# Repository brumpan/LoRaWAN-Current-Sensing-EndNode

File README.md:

# LoRaWAN-Current-Sensing-EndNode

Traditionally, remote monitoring has been done using wired communications technologies such as ethernet and fiberoptics. In the last decade, low power narrow band radio communications technologies, such as LoRaWAN, have enabled wireless remote monitoring in microgrids.  Installing remote monitoring systems can be very costly using both wired or wireless communication schemes. Wired connections are expensive during installation and wireless connections are expensive during operation due to service subscriptions and may also require pre-existing infrastructure to operate. This project provides a modular solution for monitoring power output from photovoltaic panels remotely.

This page contains the design files and software for a current-sensing end node for photovoltaic panels in microgrids using the LoRaWAN network.

# Dependencies

https://github.com/ElectronicCats/Beelan-LoRaWAN.git

https://github.com/earlephilhower/arduino-pico.git

# Credits

This project constitutes partial fulfillment of the Senior Project Capstone, a prerequisite for obtaining a Bachelor's degree in Electrical Engineering from The Oregon Institute of Technology.

Project Members: Brendan Dickerson & Leo Zenuhin

Spring 2023

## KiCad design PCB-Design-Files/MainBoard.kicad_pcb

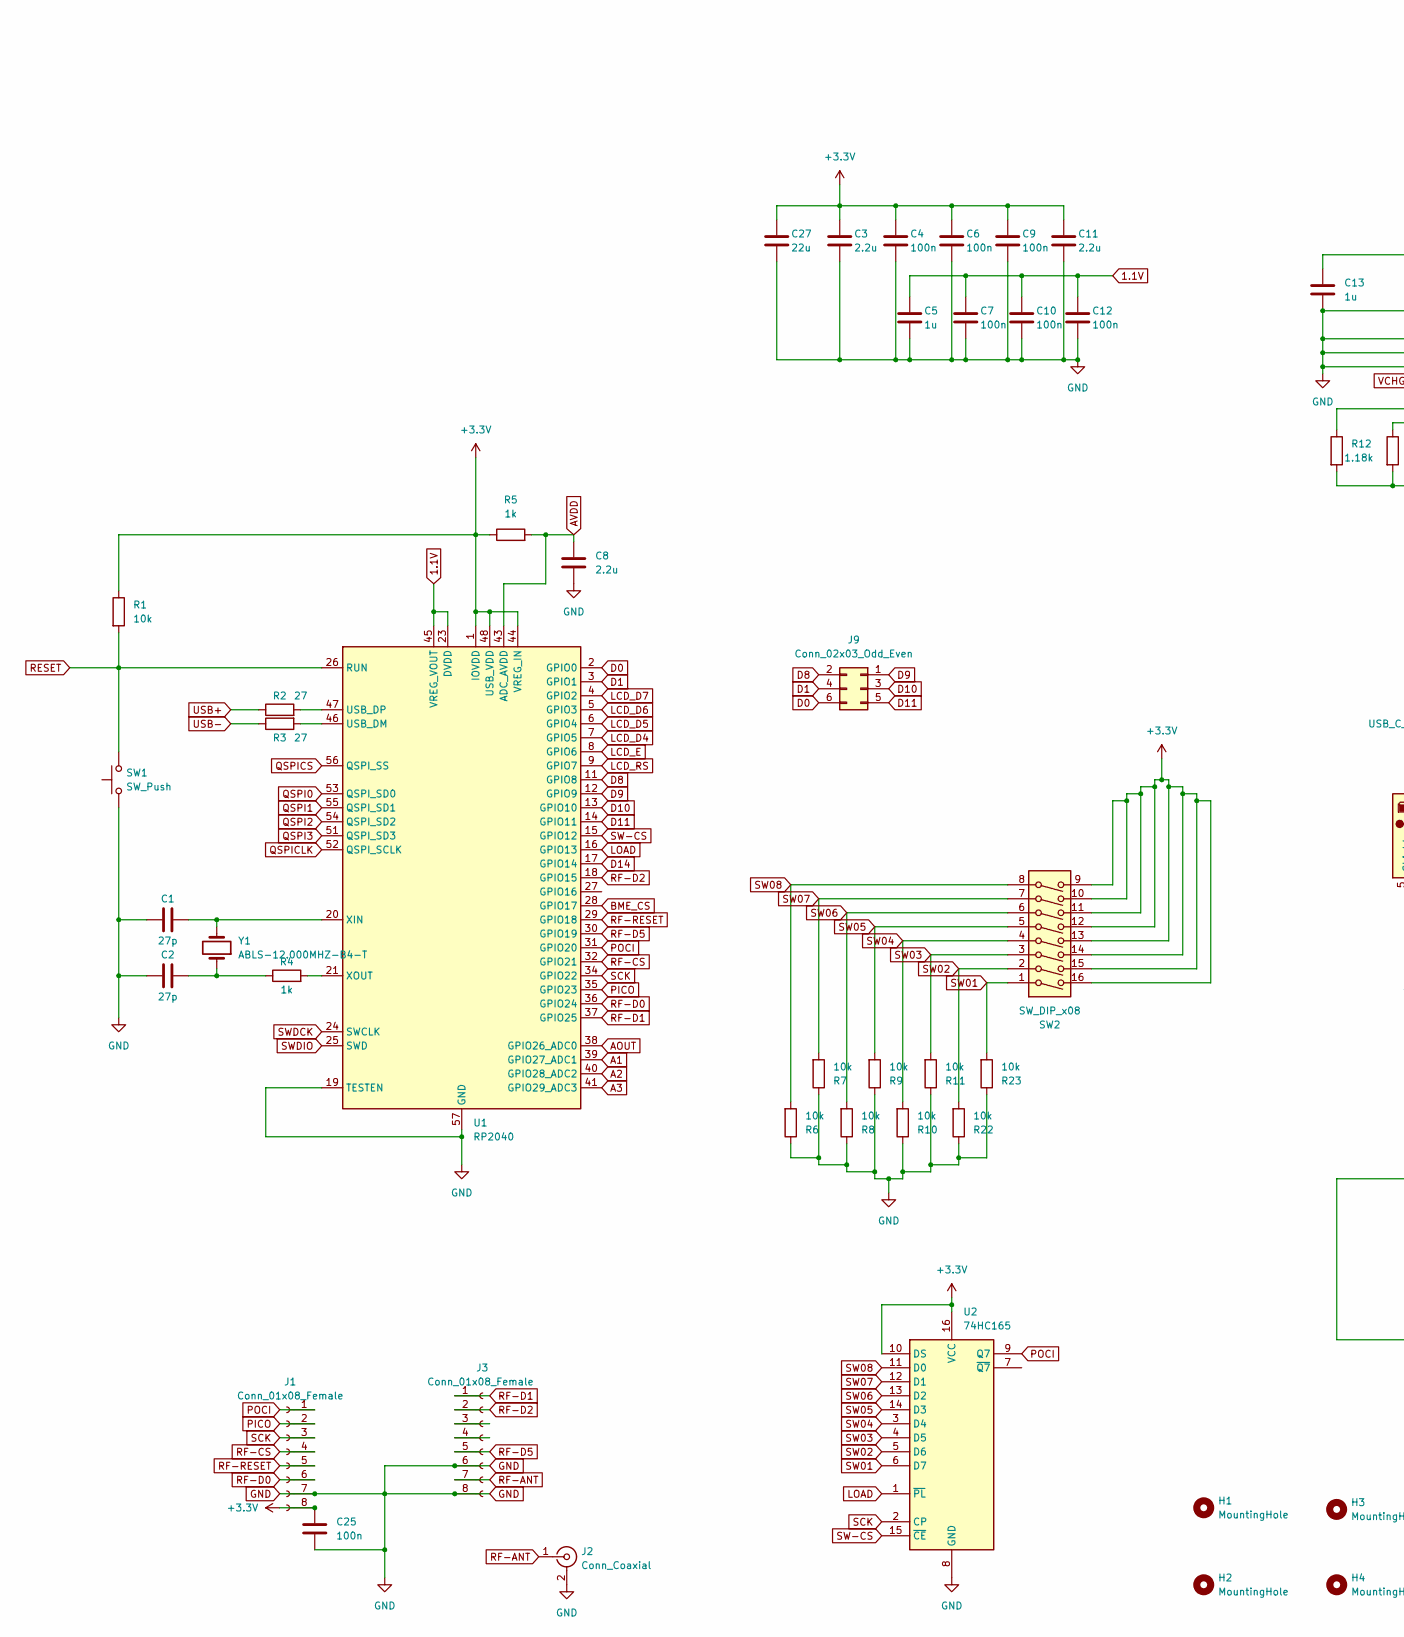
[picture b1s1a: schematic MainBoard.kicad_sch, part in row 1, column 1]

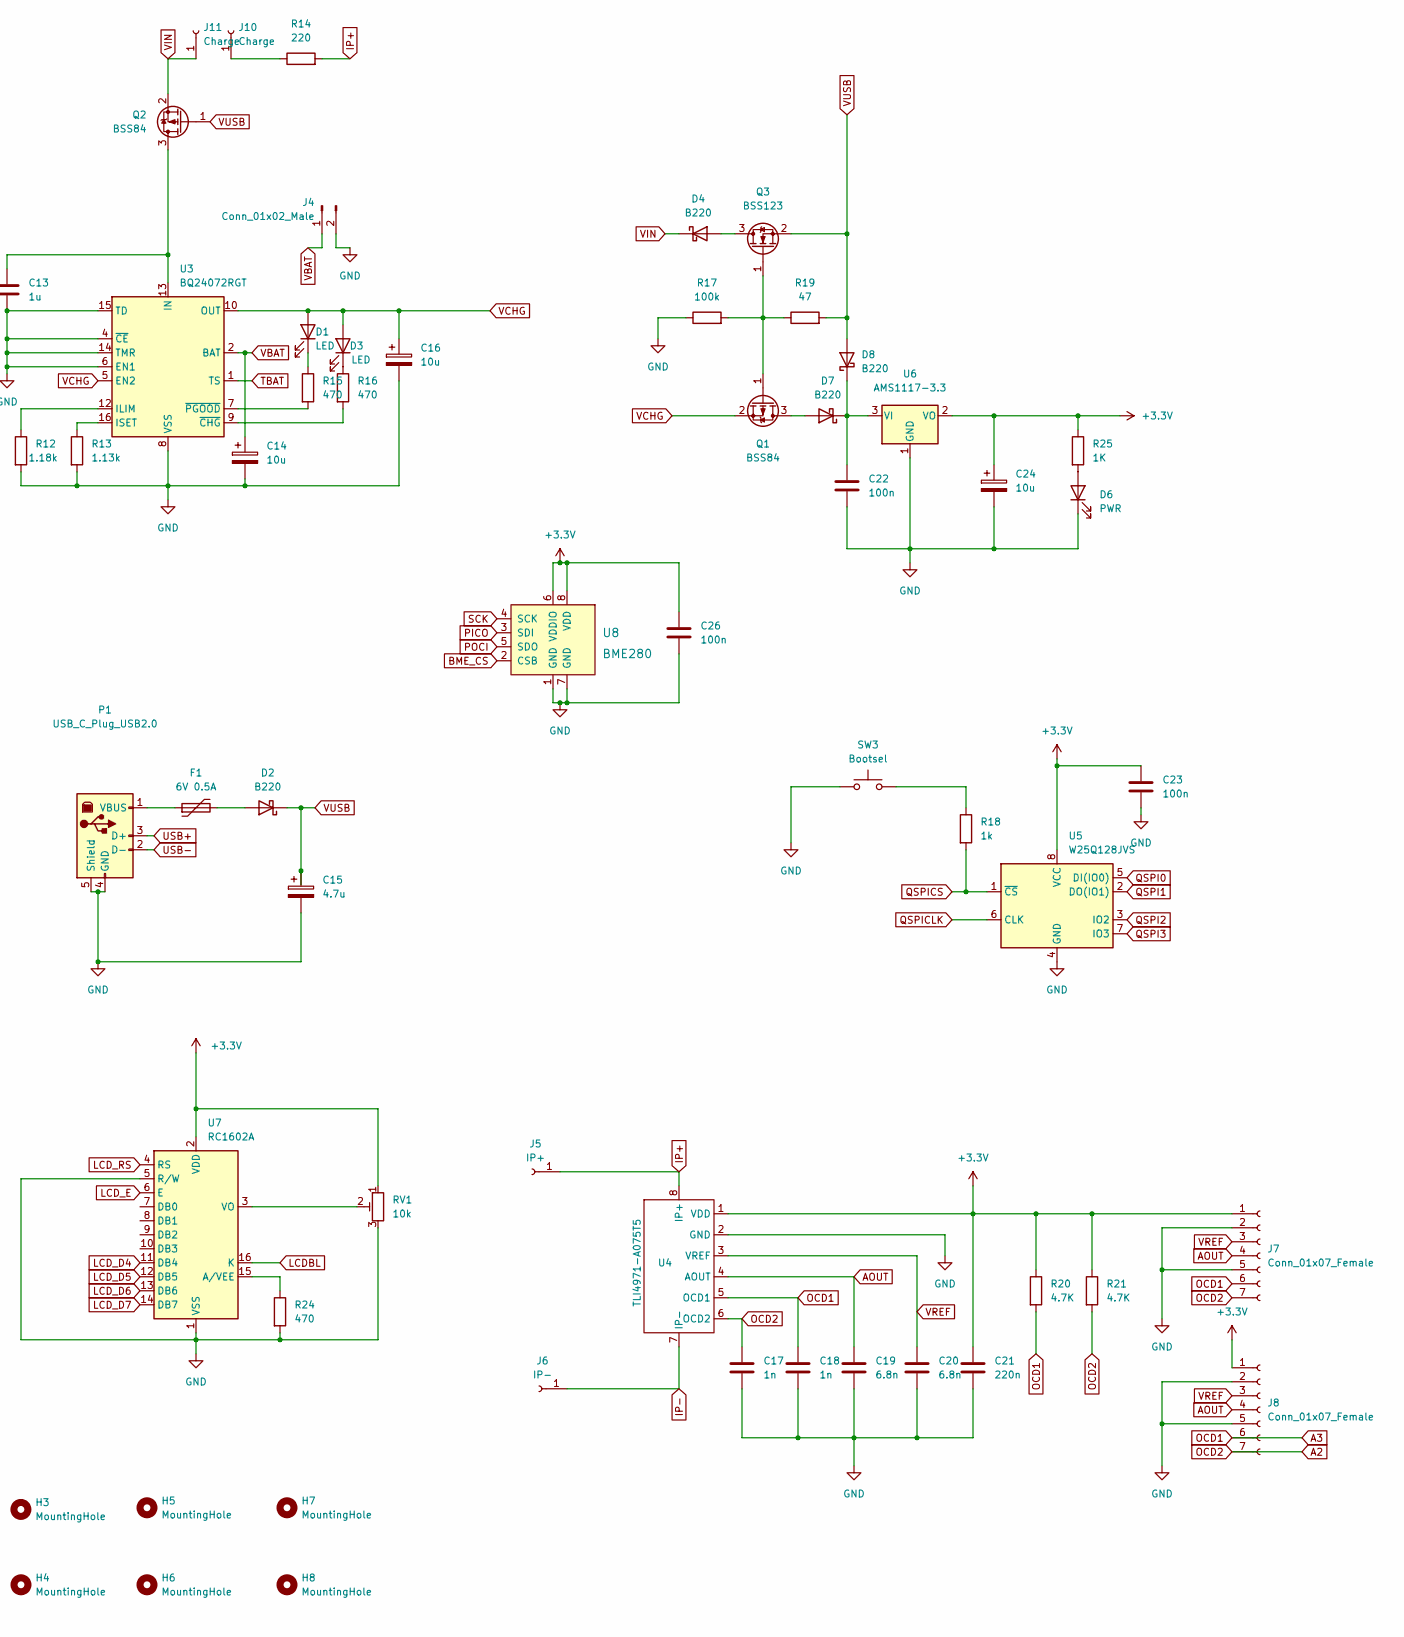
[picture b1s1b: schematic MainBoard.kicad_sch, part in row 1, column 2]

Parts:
C1, C2: 27p; C_0402_1005Metric
C3, C8, C11: 2.2u; C_0402_1005Metric
C4, C6, C7, C9, C10, C12, C22, C23, C25, C26: 100n; C_0402_1005Metric
C5, C13: 1u; C_0402_1005Metric
C14, C16, C24: 10u; C_0805_2012Metric
C15: 4.7u; C_0805_2012Metric
C17, C18: 1n; C_0402_1005Metric
C19, C20: 6.8n; C_0402_1005Metric
C21: 220n; C_0402_1005Metric
C27: 22u; CP_Elec_6.3x7.7
D1, D3: LED; LED_0805_2012Metric
D2, D4, D7, D8: B220; D_SOD-123
D6: PWR; LED_0805_2012Metric
F1: 6V 0.5A; Fuse_0805_2012Metric
H1, H2, H3, H4, H5, H6, H7, H8: MountingHole; MountingHole_2.2mm_M2
J1, J3: Conn_01x08_Female; PinHeader_1x08_P2.54mm_Vertical
J2: Conn_Coaxial; U.FL_Molex_MCRF_73412-0110_Vertical
J4: Conn_01x02_Male; JST_PH_S2B-PH-K_1x02_P2.00mm_Horizontal
J5: IP+; Wuerth_REDCUBE-THR_WP-THRSH_74651195_THR
J6: IP-; Wuerth_REDCUBE-THR_WP-THRSH_74651195_THR
J7, J8: Conn_01x07_Female; PinHeader_1x07_P2.54mm_Vertical
J9: Conn_02x03_Odd_Even; PinSocket_2x03_P2.54mm_Vertical
J10, J11: Charge; PinSocket_1x01_P2.54mm_Vertical
P1: USB_C_Plug_USB2.0; USB_B_OST_USB-B1HSxx_Horizontal
Q1, Q2: BSS84; SOT-23
Q3: BSS123; SOT-23
R1, R6, R7, R8, R9, R10, R11, R22, R23: 10k; R_0402_1005Metric
R2, R3: 27; R_0402_1005Metric
R4, R5, R18: 1k; R_0402_1005Metric
R12: 1.18k; R_0402_1005Metric
R13: 1.13k; R_0402_1005Metric
R14: 220; R_Axial_DIN0617_L17.0mm_D6.0mm_P30.48mm_Horizontal
R15, R16, R24: 470; R_0402_1005Metric
R17: 100k; R_0402_1005Metric
R19: 47; R_0402_1005Metric
R20, R21: 4.7K; R_0402_1005Metric
R25: 1K; R_0402_1005Metric
RV1: 10k; Potentiometer_Bourns_3296Y_Vertical
SW1: SW_Push; SW_PUSH_6mm
SW2: SW_DIP_x08; SW_DIP_SPSTx08_Slide_6.7x21.88mm_W7.62mm_P2.54mm_LowProfile
SW3: Bootsel; SW_PUSH_6mm
U1: RP2040; QFN-56-1EP_7x7mm_P0.4mm_EP3.2x3.2mm
U2: 74HC165; SOIC-16_3.9x9.9mm_P1.27mm
U3: BQ24072RGT; VQFN-16-1EP_3x3mm_P0.5mm_EP1.6x1.6mm
U4: TLI4971-A075T5; Infineon_PG-TISON-8-5
U5: W25Q128JVS; SOIC-8_5.23x5.23mm_P1.27mm
U6: AMS1117-3.3; SOT-223-3_TabPin2
U7: RC1602A
U8: BME280; Pressure_Sensor_LGA-8_2.5x2.5mm_BME280; MPN BME280; Digi-Key_PN 828-1063-1-ND
Y1: ABLS-12.000MHZ-B4-T; Crystal_HC49-U_Vertical

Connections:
1.1V: C5.1, C7.1, C10.1, C12.1, U1.23 (DVDD), U1.45 (VREG_VOUT), U1.50 (DVDD)
+3.3V: C3.1, C4.1, C6.1, C9.1, C11.1, C21.1, C23.1, C24.1, C25.1, C26.1, C27.1, J1.8, J7.1, J8.1, R1.1, R5.1, R20.1, R21.1, R25.1, RV1.1, SW2.9, SW2.10, SW2.11, SW2.12, SW2.13, SW2.14, SW2.15, SW2.16, U1.1 (IOVDD), U1.10 (IOVDD), U1.22 (IOVDD), U1.33 (IOVDD), U1.42 (IOVDD), U1.44 (VREG_IN), U1.48 (USB_VDD), U1.49 (IOVDD), U2.10 (DS), U2.16 (VCC), U4.1 (VDD), U5.8 (VCC), U6.2 (VO), U7.2 (VDD), U8.6 (VDDIO), U8.8 (VDD); also elsewhere on the board
A1: U1.39 (GPIO27_ADC1)
A2: C17.1, J7.7, J8.7, R21.2, U1.40 (GPIO28_ADC2), U4.6 (OCD2)
A3: C18.1, J7.6, J8.6, R20.2, U1.41 (GPIO29_ADC3), U4.5 (OCD1)
AOUT: C19.1, J7.4, J8.4, U1.38 (GPIO26_ADC0), U4.4 (AOUT)
AVDD: C8.1, R5.2, U1.43 (ADC_AVDD)
BME_CS: U1.28 (GPIO17), U8.2 (CSB)
D0: J9.6, U1.2 (GPIO0)
D1: J9.4, U1.3 (GPIO1)
D8: J9.2, U1.11 (GPIO8); also elsewhere on the board
D9: J9.1, U1.12 (GPIO9)
D10: J9.3, U1.13 (GPIO10)
D11: J9.5, U1.14 (GPIO11)
D14: U1.17 (GPIO14)
IP+: J5.1, R14.2, U4.8 (IP+)
IP-: J6.1, U4.7 (IP-)
LCDBL: U7.16 (K)
LCD_D4: U1.7 (GPIO5), U7.11 (DB4)
LCD_D5: U1.6 (GPIO4), U7.12 (DB5)
LCD_D6: U1.5 (GPIO3), U7.13 (DB6)
LCD_D7: U1.4 (GPIO2), U7.14 (DB7)
LCD_E: U1.8 (GPIO6), U7.6 (E)
LCD_RS: U1.9 (GPIO7), U7.4 (RS)
LOAD: U1.16 (GPIO13), U2.1 (~PL)
unnamed: C1.2, U1.20 (XIN), Y1.2
unnamed: C2.2, R4.1, Y1.1
unnamed: C13.1, Q2.3 (D), U3.13 (IN)
unnamed: C22.1, D7.1 (K), D8.1 (K), U6.3 (VI)
unnamed: D1.1 (K), R15.1
unnamed: D2.2 (A), F1.2
unnamed: D3.1 (K), R16.1
unnamed: D4.2 (A), Q3.3 (D)
unnamed: D6.2 (A), R25.2
unnamed: D7.2 (A), Q1.3 (D)
unnamed: F1.1, P1.1 (VBUS)
unnamed: J10.1, R14.1
unnamed: R2.2, U1.47 (USB_DP)
unnamed: R3.2, U1.46 (USB_DM)
unnamed: R4.2, U1.21 (XOUT)
unnamed: R12.1, U3.12 (ILIM)
unnamed: R13.1, U3.16 (ISET)
unnamed: R15.2, U3.7 (~PGOOD)
unnamed: R16.2, U3.9 (~CHG)
unnamed: R18.1, SW3.2
unnamed: R24.1, U7.15 (A/VEE)
unnamed: RV1.2, U7.3 (VO)
PICO: J1.2, U1.35 (GPIO23), U8.3 (SDI)
POCI: J1.1, U1.31 (GPIO20), U2.9 (Q7), U8.5 (SDO)
QSPI0: U1.53 (QSPI_SD0), U5.5 (DI(IO0))
QSPI1: U1.55 (QSPI_SD1), U5.2 (DO(IO1))
QSPI2: U1.54 (QSPI_SD2), U5.3 (IO2)
QSPI3: U1.51 (QSPI_SD3), U5.7 (IO3)
QSPICLK: U1.52 (QSPI_SCLK), U5.6 (CLK)
QSPICS: R18.2, U1.56 (QSPI_SS), U5.1 (~CS)
RESET: R1.2, SW1.2, U1.26 (RUN)
RF-ANT: J2.1 (In), J3.7
RF-CS: J1.4, U1.32 (GPIO21)
RF-D0: J1.6, U1.36 (GPIO24)
RF-D1: J3.1, U1.37 (GPIO25)
RF-D2: J3.2, U1.18 (GPIO15)
RF-D5: J3.5, U1.30 (GPIO19)
RF-RESET: J1.5, U1.29 (GPIO18)
SCK: J1.3, U1.34 (GPIO22), U2.2 (CP), U8.4 (SCK)
SW01: R23.2, SW2.1, U2.6 (D7)
SW02: R22.2, SW2.2, U2.5 (D6)
SW03: R11.2, SW2.3, U2.4 (D5)
SW04: R10.2, SW2.4, U2.3 (D4)
SW05: R9.2, SW2.5, U2.14 (D3)
SW06: R8.2, SW2.6, U2.13 (D2)
SW07: R7.2, SW2.7, U2.12 (D1)
SW08: R6.2, SW2.8, U2.11 (D0)
SW-CS: U1.15 (GPIO12), U2.15 (~CE)
SWDCK: U1.24 (SWCLK)
SWDIO: U1.25 (SWD)
TBAT: U3.1 (TS)
USB+: P1.3 (D+), R2.1
USB-: P1.2 (D-), R3.1
VBAT: C14.1, J4.1, U3.2 (BAT), U3.3 (BAT)
VCHG: C16.1, D1.2 (A), D3.2 (A), Q1.2 (S), U3.5 (EN2), U3.10 (OUT), U3.11 (OUT)
VREF: C20.1, J7.3, J8.3, U4.3 (VREF)

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
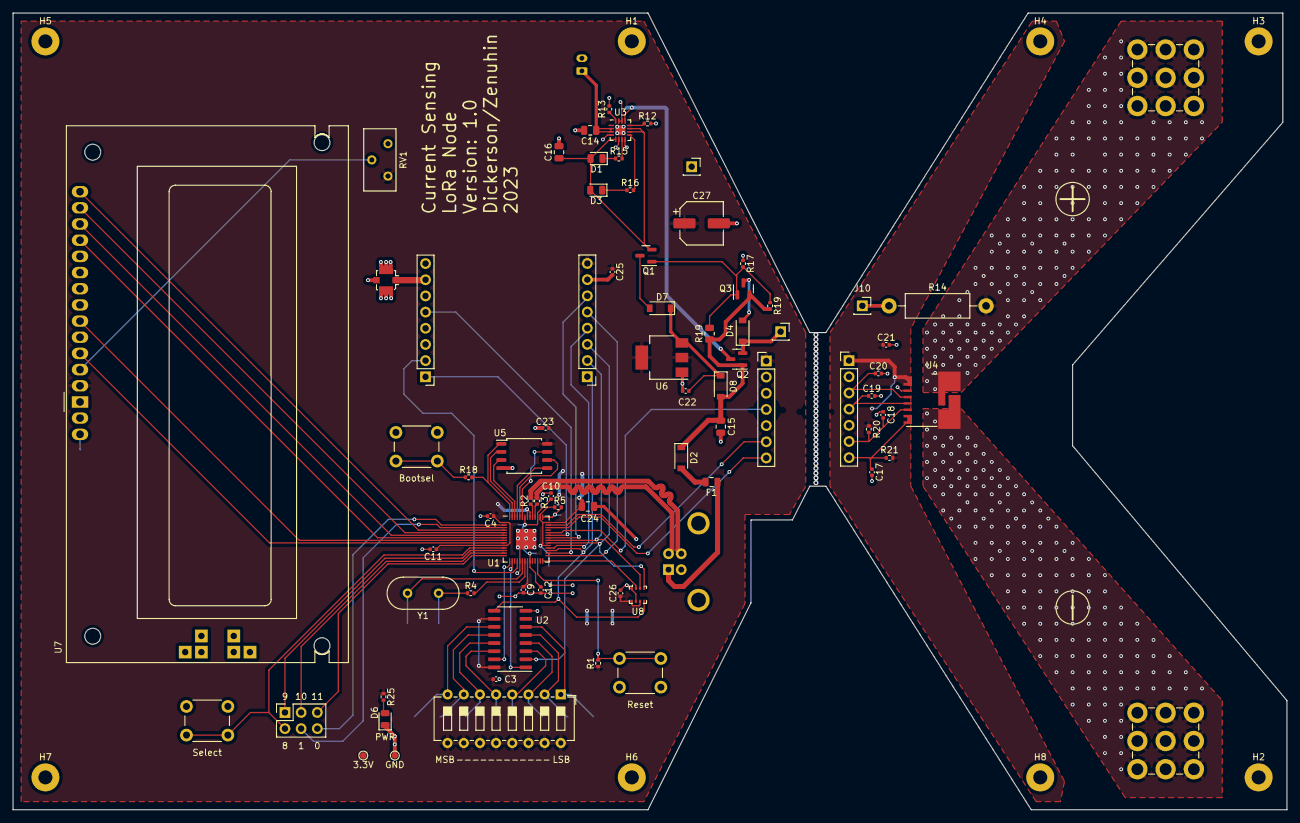
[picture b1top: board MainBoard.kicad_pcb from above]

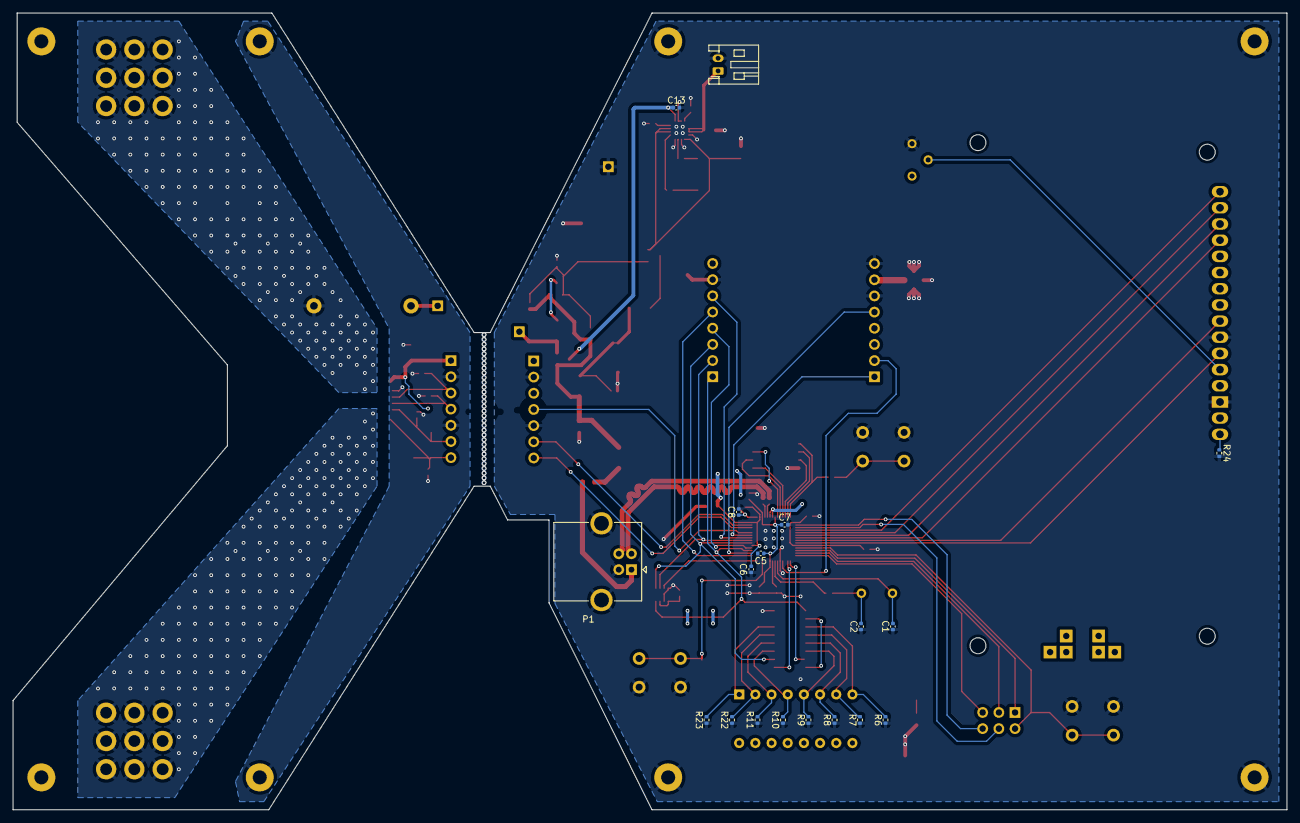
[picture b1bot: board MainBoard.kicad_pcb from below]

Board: 2 copper layers, 200.0 x 125.1 mm, 101 parts (18 on the bottom side), 79 nets.

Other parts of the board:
3.3V: TestPoint_Pad_D1.0mm
GND: TestPoint_Pad_D1.0mm
J11#2: Charge; PinSocket_1x01_P2.54mm_Vertical
R19#2: 47; R_0402_1005Metric
SW1#2: Select; SW_PUSH_6mm

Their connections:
+3.3V: 3.3V.1; also elsewhere on the board
D8: SW1#2.1; also elsewhere on the board

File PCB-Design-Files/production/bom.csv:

Designator,Footprint,Quantity,Value,LCSC Part #
"C1, C2",402,2,27p,
"C10, C12, C22, C23, C25, C26, C4, C6, C7, C9",402,10,100n,
"C11, C3, C8",402,3,2.2u,
"C13, C5",402,2,1u,
"C14, C16, C24",805,3,10u,
C15,805,1,4.7u,
"C17, C18",402,2,1n,
"C19, C20",402,2,6.8n,
C21,402,1,220n,
C27,CP_Elec_6.3x7.7,1,22u,
"D1, D3",805,2,LED,
"D2, D4, D7, D8",D_SOD-123,4,B220,
D6,805,1,PWR,
F1,805,1,6V 0.5A,
"Q1, Q2",SOT-23,2,BSS84,
Q3,SOT-23,1,BSS123,
"R1, R10, R11, R22, R23, R6, R7, R8, R9",402,9,10k,
R12,402,1,1.18k,
R13,402,1,1.13k,
R14,R_Axial_DIN0411_L9.9mm_D3.6mm_P15.24mm_Horizontal,1,220,
"R15, R16, R24",402,3,470,
R17,402,1,100k,
"R18, R25, R4, R5",402,4,1k,
R19_2,805,1,47,
R19,402,1,47,
"R2, R3",402,2,27,
"R20, R21",402,2,4.7K,
SW1,SW_PUSH_6mm,1,Select,
SW2,SW_DIP_SPSTx08_Slide_6.7x21.88mm_W7.62mm_P2.54mm_LowProfile,1,SW_DIP_x08,
SW3,SW_PUSH_6mm,1,Bootsel,
U1,QFN-56-1EP_7x7mm_P0.4mm_EP3.2x3.2mm,1,RP2040,
U2,SOIC-16_3.9x9.9mm_P1.27mm,1,74HC165,
U3,VQFN-16-1EP_3x3mm_P0.5mm_EP1.6x1.6mm,1,BQ24072RGT,
U5,SOIC-8_5.23x5.23mm_P1.27mm,1,W25Q128JVS,
U6,SOT-223-3_TabPin2,1,AMS1117-3.3,

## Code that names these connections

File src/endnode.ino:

#include <Adafruit_BME280.h>
#include <LiquidCrystal.h>
#include <lorawan.h>
#include <SPI.h>
#include <TLI4971.h>

/***************************************************************

- File:   endnode.ino
- Author: Brendan Dickerson
- Date:   2023-05-31
- Course: Capstone Project Spring 2023
- School: Oregon Institue of Technology
- Description:
    End node takes an analog current reading, environment status,
    and additional information and transmits it back to a 
    LoraWAN gateway. Typical applications for this include
    remote alternative energy sources such as photovoltaic 
    installations or wind energy farms. 

****************************************************************/

// RP2040 pin definitions
#define D0      0
#define D1      1
#define LCD_D7  2
#define LCD_D6  3
#define LCD_D5  4
#define LCD_D4  5
#define LCD_E   6
#define LCD_RS  7
#define SELBTN  8
#define TXLED   9
#define LCDBL   10
#define D11     11
#define SW_CS   12
#define LOAD    13
#define D14     14
#define RF_D2   15
#define BME_CS  17
#define RF_RES  18
#define RF_D5   19
#define POCI    20
#define RF_CS   21
#define SCK     22
#define PICO    23
#define RF_D0   24
#define RF_D1   25
#define CURRENT A0
#define VREF    A2
#define OCD1    A3


// //LCD Display
// LiquidCrystal lcd(LCD_RS, LCD_E, LCD_D4, LCD_D5, LCD_D6, LCD_D7);
// bool displayActive = false;

// //BME280
// //Adafruit_BME280 bme(BME_CS, POCI, PICO, SCK);
// long temp = 0;
// long humidity = 0;

//ABP Credentials 
const char *devAddr = "10101010";
const char *nwkSKey = "00000000000000000000000000000000";
const char *appSKey = "00000000000000000000000000000000";

//Timing for transmission
const unsigned long interval = 10000;    // interval to send message
unsigned long previousMillis = 0;  // will store last time message sent
unsigned int counter = 0;     // message counter

//Storage for current calculation
int current = 0;
int avg,ref = 0;

//Storage for transmission data
char data[2] = {0, 1};
byte recvStatus = 0;

//Pinout for RFM95
const sRFM_pins RFM_pins = {
  .CS = RF_CS,
  .RST = RF_RES,
  .DIO0 = RF_D0,
  .DIO1 = RF_D1,
  .DIO2 = RF_D2,
  .DIO5 = RF_D5,
};

/******************
  Setup Function
******************/
void setup() {
  Serial.begin(9600);
  delay(100);
  //while(!Serial);
  loraSetup();
  //bmeSetup();
  //lcd.begin(16, 2);

  pinMode(LCDBL, OUTPUT);
  pinMode(VREF, INPUT);
  pinMode(CURRENT, INPUT);
  pinMode(TXLED, OUTPUT);
  analogWrite(VREF, 1028);
}

/*******************
  Loop Function
*******************/
void loop() {
  transmit();
  digitalWrite(TXLED, LOW);
  digitalWrite(LCDBL, HIGH);
}

/*******************
  Read TLI4971
*******************/
void getCurrent() {
  avg = 0;
  for(int i = 0; i<500; i++) {
    analogRead(CURRENT);
    avg += analogRead(CURRENT);
  }
  avg = avg/500.0;
  
  ref = 0;
  for(int i = 0; i<500; i++) {
    analogRead(VREF);
    ref += analogRead(VREF);
  }
  ref = ref/500.0;
  
  current = round(((avg-ref)/6));
}

/*******************
  LoRa Transmit
*******************/
void transmit() {
  // Check interval overflow
  if(millis() - previousMillis > interval) {
    //getEnvironment();
    getCurrent();
    Serial.println(current);
    digitalWrite(TXLED, HIGH);
    digitalWrite(LCDBL, HIGH);
    //lcd.clear();
    //lcd.print("Transmitting...");
    previousMillis = millis(); 
    data[0] = current;     //change to current
    Serial.print("Sending: ");
    Serial.println((int)data[0]);

    lora.sendUplink(data, strlen(data), 0, 1);
    counter++;
  }
  lora.update(); //needed 
}

/*******************
  LoRa Setup/Config
*******************/
void loraSetup() {
  while(!lora.init()){
    Serial.println("RFM95 not detected");
    delay(1000);
  }
  Serial.println("Starting...");
  
  // Set LoRaWAN Class change CLASS_A or CLASS_C
  lora.setDeviceClass(CLASS_A);

  // Set Data Rate
  lora.setDataRate(SF9BW125);
  
  // set channel to random
  lora.setChannel(MULTI);
  
  // Put ABP Key and DevAddress here
  lora.setNwkSKey(nwkSKey);
  lora.setAppSKey(appSKey);
  lora.setDevAddr(devAddr);
  lora.setDevEUI("00000000");
}

/*******************
  Setup BME280
*******************/
// void bmeSetup() {
//     unsigned status;
//     // default settings
//    // status = bme.begin();  
//     // You can also pass in a Wire library object like &Wire2
//     // status = bme.begin(0x76, &Wire2)
//     if (!status) {
//         Serial.println("Could not find a valid BME280 sensor, check wiring, address, sensor ID!");
//         Serial.print("SensorID was: 0x"); Serial.println(bme.sensorID(),16);
//         Serial.print("        ID of 0xFF probably means a bad address, a BMP 180 or BMP 085\n");
//         Serial.print("   ID of 0x56-0x58 represents a BMP 280,\n");
//         Serial.print("        ID of 0x60 represents a BME 280.\n");
//         Serial.print("        ID of 0x61 represents a BME 680.\n");
//         while (1) delay(10);
//     }
// }

/*******************
  Read BME280
*******************/
// void getEnvironment() {
//   //temp = bme.readTemperature();
//   Serial.print("Temperature = ");
//   Serial.print(temp);
//   Serial.println(" °C");
    
//   humidity = bme.readHumidity();
//   Serial.print("Humidity = ");
//   Serial.print(humidity);
//   Serial.println(" %");
// }

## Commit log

2023-05-24 Board files for Arduino IDE
2023-05-24 PCB Design Files in KiCAD
2023-05-24 Arduino program file for board
2023-05-24 Custom board files for end node
